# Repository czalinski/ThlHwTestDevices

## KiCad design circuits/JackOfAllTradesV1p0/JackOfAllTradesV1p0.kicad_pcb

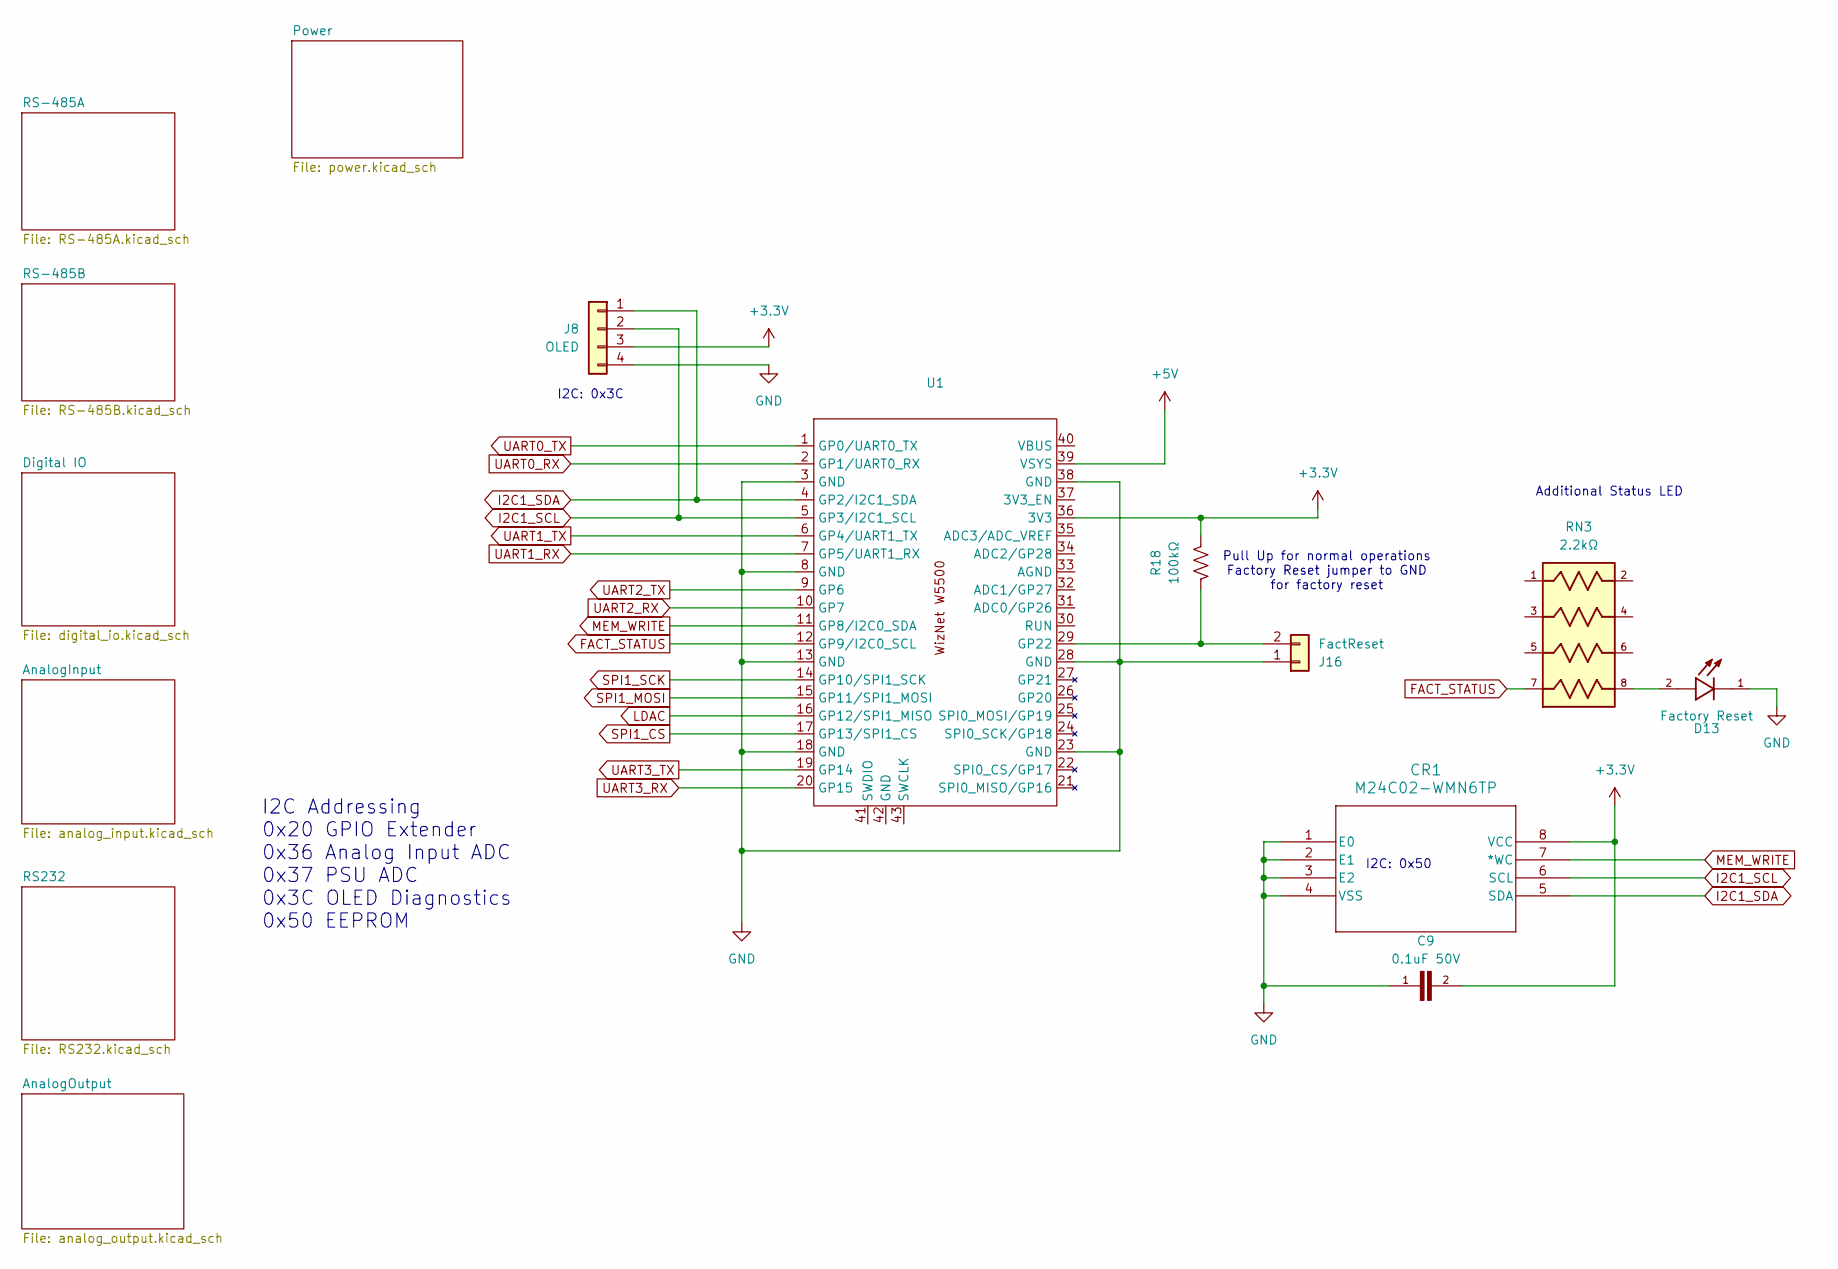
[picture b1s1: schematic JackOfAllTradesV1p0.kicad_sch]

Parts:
C9: 0.1uF 50V; CAPC2012X70
CR1: M24C02-WMN6TP; SO-8_STM
D13: Factory Reset; LED_LTST-C170GKT; PARTREV I
J8: OLED; PinHeader_1x04_P2.54mm_Vertical
J16: FactReset; PinHeader_1x02_P2.54mm_Horizontal
R18: 100kΩ; RES_1206
RN3: 2.2kΩ; RESCAXS50P200X100X55-8N
U1: WizNetPico_OnBoard

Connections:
+3.3V: C9.2, CR1.8 (VCC), J8.3, R18.1, U1.36 (3V3); also elsewhere on the board
+5V: U1.39 (VSYS); also elsewhere on the board
FACT_STATUS: RN3.7, U1.12 (GP9/I2C0_SCL)
GND: C9.1, CR1.1 (E0), CR1.2 (E1), CR1.3 (E2), CR1.4 (VSS), D13.1, J8.4, J16.1, U1.3 (GND), U1.8 (GND), U1.13 (GND), U1.18 (GND), U1.23 (GND), U1.28 (GND), U1.38 (GND); also elsewhere on the board
I2C1_SCL: CR1.6 (SCL), J8.2, U1.5 (GP3/I2C1_SCL); also elsewhere on the board
I2C1_SDA: CR1.5 (SDA), J8.1, U1.4 (GP2/I2C1_SDA); also elsewhere on the board
LDAC: U1.16 (GP12/SPI1_MISO); also elsewhere on the board
MEM_WRITE: CR1.7 (*WC), U1.11 (GP8/I2C0_SDA)
unnamed: D13.2, RN3.8
unnamed: J16.2, R18.2, U1.29 (GP22)
SPI1_CS: U1.17 (GP13/SPI1_CS); also elsewhere on the board
SPI1_MOSI: U1.15 (GP11/SPI1_MOSI); also elsewhere on the board
SPI1_SCK: U1.14 (GP10/SPI1_SCK); also elsewhere on the board
UART0_RX: U1.2 (GP1/UART0_RX); also elsewhere on the board
UART0_TX: U1.1 (GP0/UART0_TX); also elsewhere on the board
UART1_RX: U1.7 (GP5/UART1_RX); also elsewhere on the board
UART1_TX: U1.6 (GP4/UART1_TX); also elsewhere on the board
UART2_RX: U1.10 (GP7); also elsewhere on the board
UART2_TX: U1.9 (GP6); also elsewhere on the board
UART3_RX: U1.20 (GP15); also elsewhere on the board
UART3_TX: U1.19 (GP14); also elsewhere on the board

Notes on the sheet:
Pull Up for normal operations Factory Reset jumper to GND for factory reset
I2C: 0x3C
Additional Status LED
I2C Addressing 0x20 GPIO Extender 0x36 Analog Input ADC 0x37 PSU ADC 0x3C OLED Diagnostics 0x50 EEPROM
I2C: 0x50

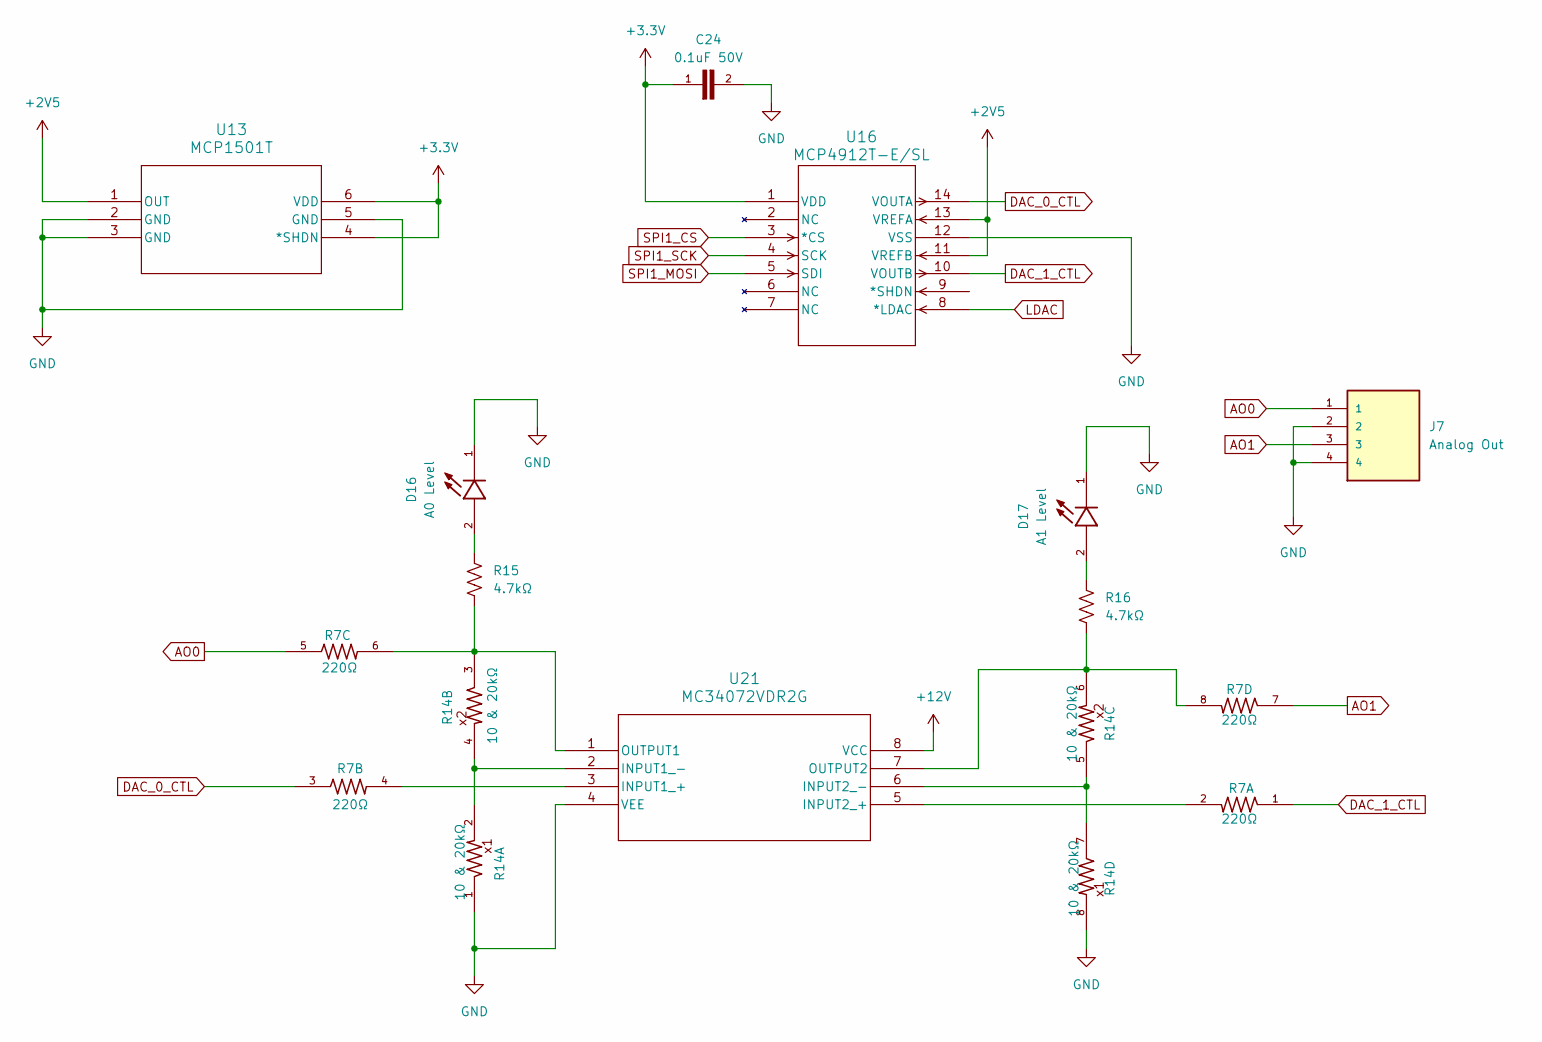
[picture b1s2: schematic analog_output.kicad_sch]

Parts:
C24: 0.1uF 50V; CAPC2012X70
D16: A0 Level; LED_LTST-C170GKT; PARTREV I
D17: A1 Level; LED_LTST-C170GKT; PARTREV I
J7: Analog Out; TE_1985218; PARTREV 29.03.2021
R7: 220Ω; RESCAV80P320X160X70-8N
R14: 10 & 20kΩ; RESCAV80P320X160X70-8N
R15, R16: 4.7kΩ; RES_1206
U13: MCP1501T; SOT-23_OT&slash_OTY_MCH
U16: MCP4912T-E/SL; SOIC14-N_MC_MCH
U21: MC34072VDR2G; SOIC8_ONS

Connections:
+2V5: U13.1 (OUT), U16.11 (VREFB), U16.13 (VREFA)
+3.3V: C24.1, U13.4 (*SHDN), U13.6 (VDD), U16.1 (VDD); also elsewhere on the board
+12V: U21.8 (VCC); also elsewhere on the board
AO0: J7.1, R7.5
AO1: J7.3, R7.7
DAC_0_CTL: R7.3, U16.14 (VOUTA)
DAC_1_CTL: R7.1, U16.10 (VOUTB)
GND: C24.2, D16.1, D17.1, J7.2, J7.4, R14.1, R14.8, U13.2 (GND), U13.3 (GND), U13.5 (GND), U16.12 (VSS), U21.4 (VEE); also elsewhere on the board
LDAC: U16.8 (*LDAC); also elsewhere on the board
unnamed: D16.2, R15.1
unnamed: D17.2, R16.1
unnamed: R7.4, U21.3 (INPUT1_+)
unnamed: R14.2, R14.4, U21.2 (INPUT1_-)
unnamed: R7.2, U21.5 (INPUT2_+)
unnamed: R14.5, R14.7, U21.6 (INPUT2_-)
unnamed: R7.6, R14.3, R15.2, U21.1 (OUTPUT1)
unnamed: R7.8, R14.6, R16.2, U21.7 (OUTPUT2)
SPI1_CS: U16.3 (*CS); also elsewhere on the board
SPI1_MOSI: U16.5 (SDI); also elsewhere on the board
SPI1_SCK: U16.4 (SCK); also elsewhere on the board

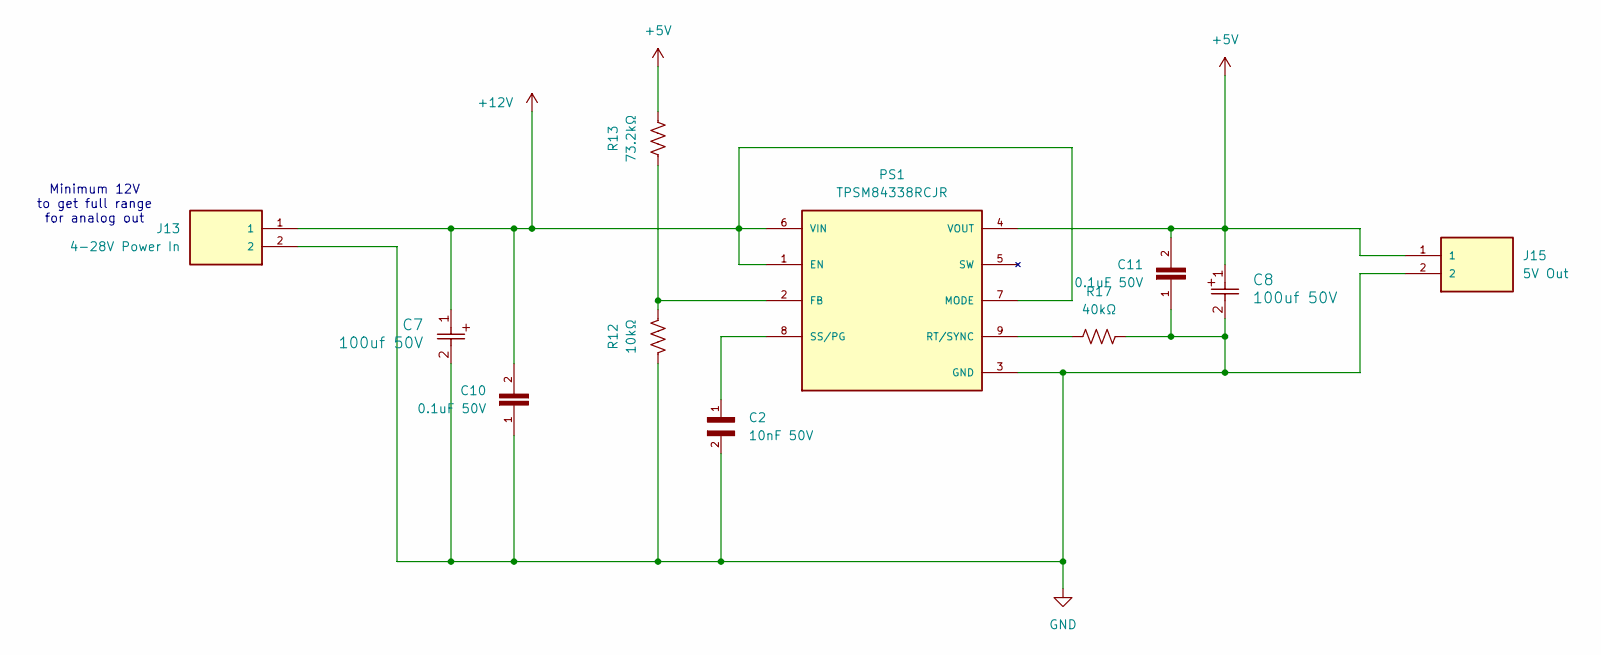
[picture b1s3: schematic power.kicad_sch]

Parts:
C2: 10nF 50V; CAPC3216X90N; PARTREV Jul. 2024
C7, C8: 100uf 50V; CAP_YX_8X11P5_RUB
C10, C11: 0.1uF 50V; CAPC2012X70
J13: 4-28V Power In; CUI_TB005-762-02BE
J15: 5V Out; CUI_TB005-762-02BE
PS1: TPSM84338RCJR; CONV_TPSM84338RCJR; PARTREV November 2024
R12: 10kΩ; RES_1206
R13: 73.2kΩ; RES_1206
R17: 40kΩ; RES_1206

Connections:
+5V: C8.1, C11.2, J15.1, PS1.4 (VOUT_4), PS1.4_1 (VOUT_4), PS1.4_2 (VOUT_4), PS1.4_3 (VOUT_4), PS1.4_4 (VOUT_4), PS1.4_5 (VOUT_4), PS1.4_6 (VOUT_4), R13.2; also elsewhere on the board
+12V: C7.1, C10.2, J13.1, PS1.1 (EN_1), PS1.6 (VIN_6), PS1.7 (MODE_7); also elsewhere on the board
GND: C2.2, C7.2, C8.2, C10.1, C11.1, J13.2, J15.2, PS1.3 (GND_3), R12.2, R17.2; also elsewhere on the board
unnamed: PS1.2 (FB_2), R12.1, R13.1
unnamed: PS1.9 (RT/SYNC_9), R17.1
unnamed: C2.1, PS1.8 (SS/PG_8)

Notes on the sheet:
Minimum 12V to get full range for analog out

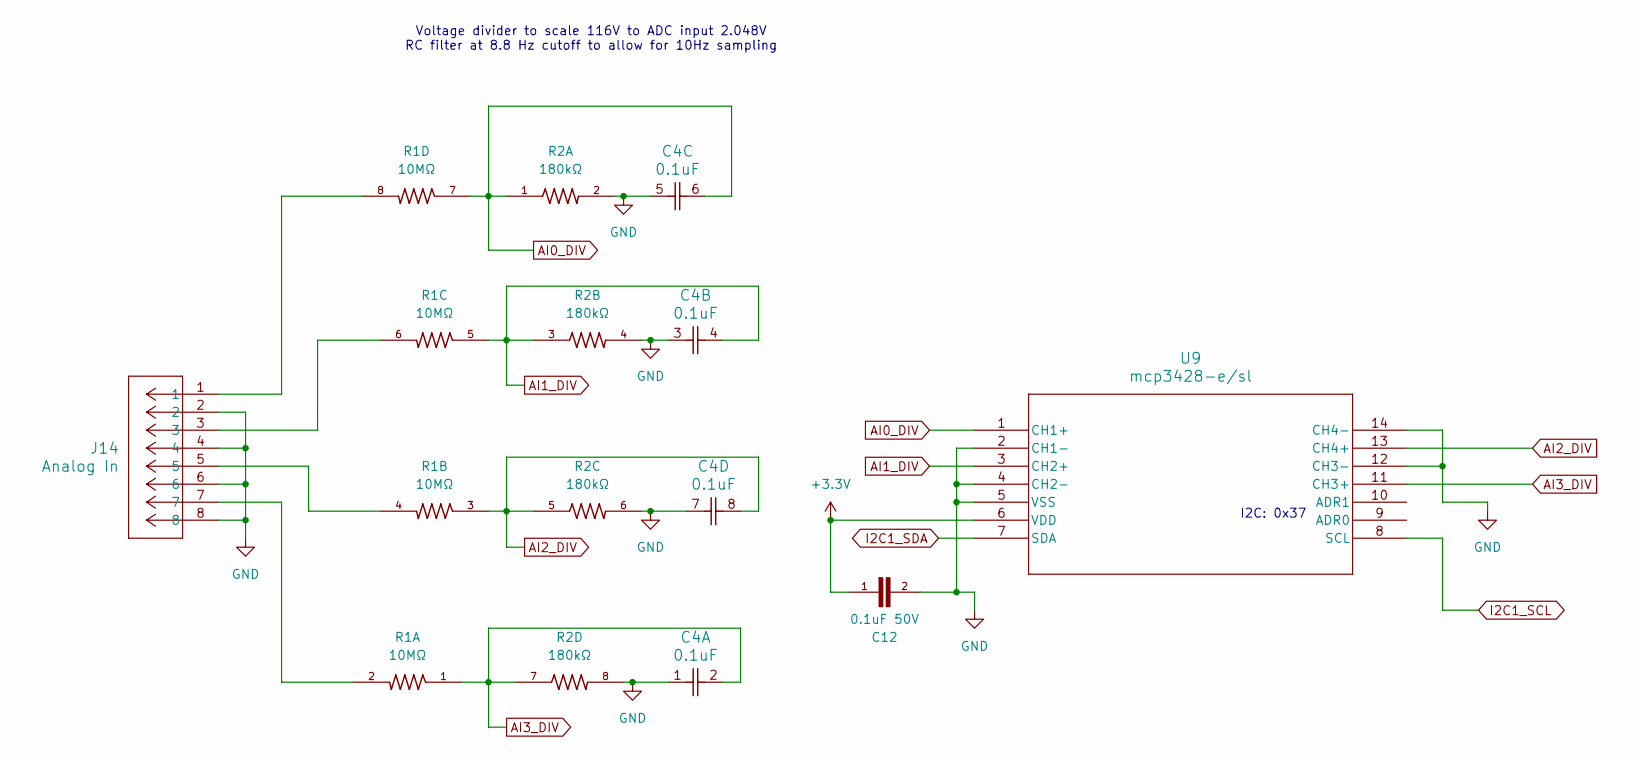
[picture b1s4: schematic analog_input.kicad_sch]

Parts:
C4: 0.1uF; CAP_CA0612_3P2X1P6_YAG
C12: 0.1uF 50V; CAPC2012X70
J14: Analog In; CONN_1989803_PXC
R1: 10MΩ; RESCAV80P320X160X70-8N
R2: 180kΩ; RESCAV80P320X160X70-8N
U9: mcp3428-e/sl; SOIC14-N_MC_MCH

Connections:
+3.3V: C12.1, U9.6 (VDD); also elsewhere on the board
AI0_DIV: C4.6, R1.7, R2.1, U9.1 (CH1+)
AI1_DIV: C4.4, R1.5, R2.3, U9.3 (CH2+)
AI2_DIV: C4.8, R1.3, R2.5, U9.13 (CH4+)
AI3_DIV: C4.2, R1.1, R2.7, U9.11 (CH3+)
GND: C4.1, C4.3, C4.5, C4.7, C12.2, J14.2, J14.4, J14.6, J14.8, R2.2, R2.4, R2.6, R2.8, U9.2 (CH1-), U9.4 (CH2-), U9.5 (VSS), U9.12 (CH3-), U9.14 (CH4-); also elsewhere on the board
I2C1_SCL: U9.8 (SCL); also elsewhere on the board
I2C1_SDA: U9.7 (SDA); also elsewhere on the board
unnamed: J14.1, R1.8
unnamed: J14.3, R1.6
unnamed: J14.5, R1.4
unnamed: J14.7, R1.2

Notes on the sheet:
Voltage divider to scale 116V to ADC input 2.048V RC filter at 8.8 Hz cutoff to allow for 10Hz sampling
I2C: 0x37

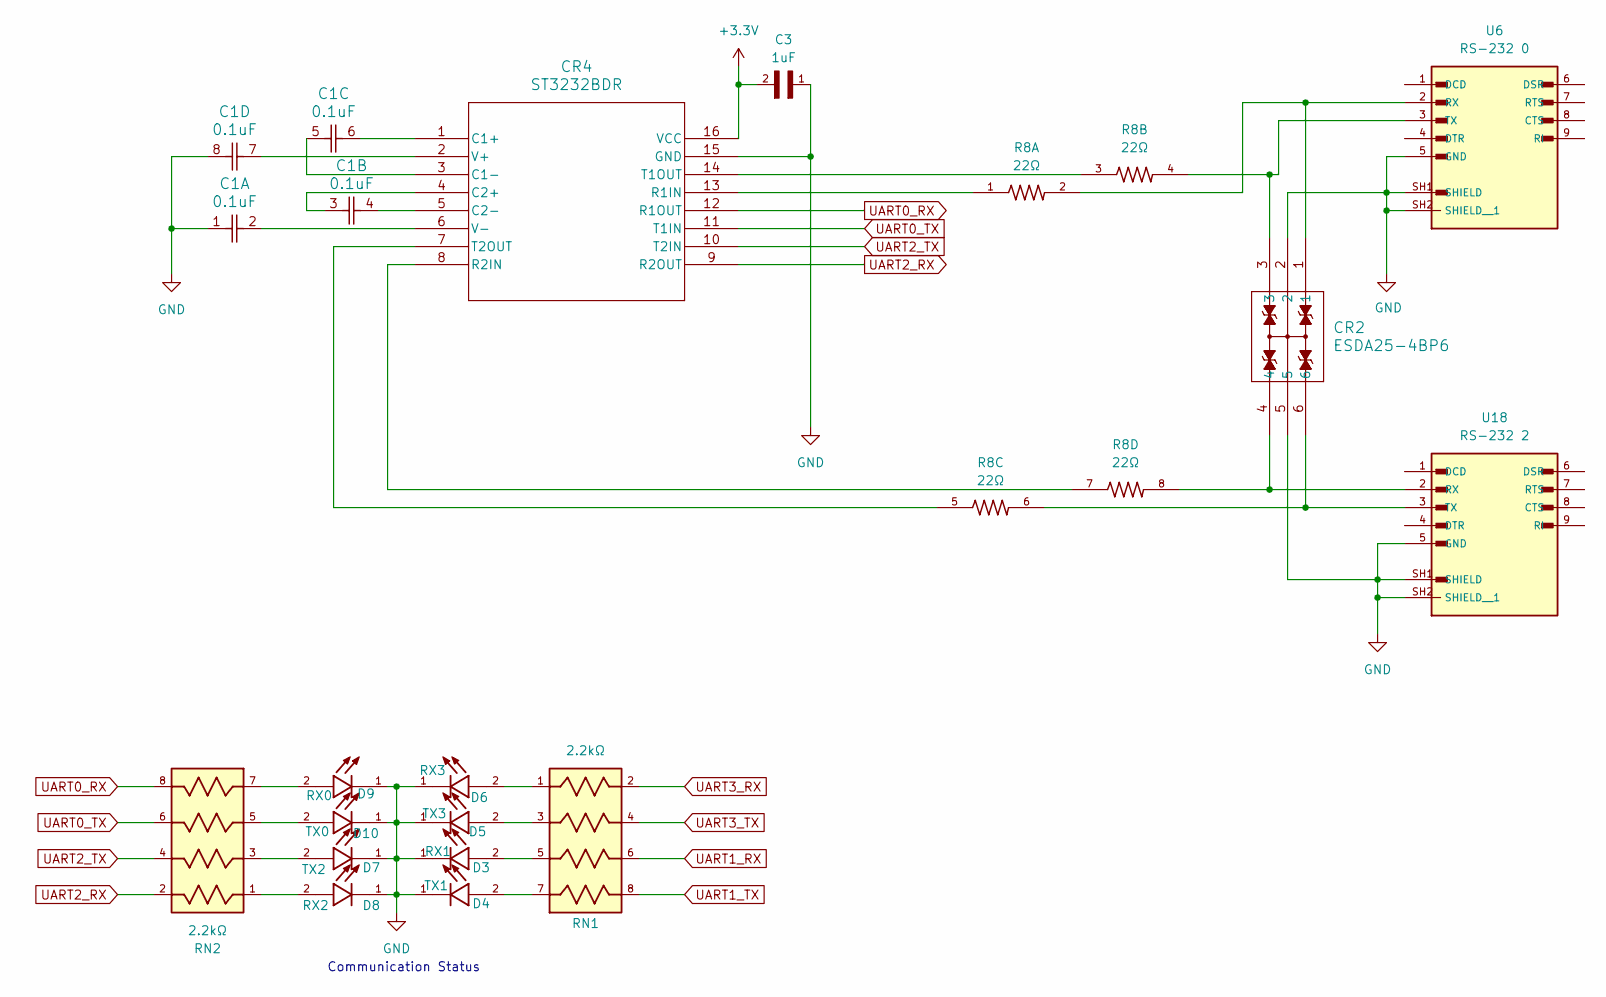
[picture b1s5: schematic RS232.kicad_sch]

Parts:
C1: 0.1uF; CAP_CA0612_3P2X1P6_YAG
C3: 1uF; CAPC1608X90N
CR2: ESDA25-4BP6; SOT666_ESDA25_STM
CR4: ST3232BDR; SO-16_STM
D3: RX1; LED_LTST-C170GKT; PARTREV I
D4: TX1; LED_LTST-C170GKT; PARTREV I
D5: TX3; LED_LTST-C170GKT; PARTREV I
D6: RX3; LED_LTST-C170GKT; PARTREV I
D7: TX2; LED_LTST-C170GKT; PARTREV I
D8: RX2; LED_LTST-C170GKT; PARTREV I
D9: RX0; LED_LTST-C170GKT; PARTREV I
D10: TX0; LED_LTST-C170GKT; PARTREV I
R8: 22Ω; RESCAV80P320X160X70-8N
RN1, RN2: 2.2kΩ; RESCAXS50P200X100X55-8N
U6: RS-232 0; ASSMANN_A-DS_09_A_KG-T2S
U18: RS-232 2; ASSMANN_A-DS_09_A_KG-T2S

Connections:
+3.3V: C3.2, CR4.16 (VCC); also elsewhere on the board
GND: C1.1, C1.8, C3.1, CR2.2, CR2.5, CR4.15 (GND), D3.1, D4.1, D5.1, D6.1, D7.1, D8.1, D9.1, D10.1, U6.5 (GND), U6.SH1 (SHIELD), U6.SH2 (SHIELD__1), U18.5 (GND), U18.SH1 (SHIELD), U18.SH2 (SHIELD__1); also elsewhere on the board
unnamed: C1.6, CR4.1 (C1+)
unnamed: C1.5, CR4.3 (C1-)
unnamed: C1.3, CR4.4 (C2+)
unnamed: C1.4, CR4.5 (C2-)
unnamed: CR4.13 (R1IN), R8.1
unnamed: CR4.8 (R2IN), R8.7
unnamed: CR4.14 (T1OUT), R8.3
unnamed: CR4.7 (T2OUT), R8.5
unnamed: C1.7, CR4.2 (V+)
unnamed: C1.2, CR4.6 (V-)
unnamed: D3.2, RN1.5
unnamed: D4.2, RN1.7
unnamed: D5.2, RN1.3
unnamed: D6.2, RN1.1
unnamed: D7.2, RN2.3
unnamed: D8.2, RN2.1
unnamed: D9.2, RN2.7
unnamed: D10.2, RN2.5
unnamed: CR2.1, R8.2, U6.2 (RX)
unnamed: CR2.3, R8.4, U6.3 (TX)
unnamed: CR2.4, R8.8, U18.2 (RX)
unnamed: CR2.6, R8.6, U18.3 (TX)
UART0_RX: CR4.12 (R1OUT), RN2.8; also elsewhere on the board
UART0_TX: CR4.11 (T1IN), RN2.6; also elsewhere on the board
UART1_RX: RN1.6; also elsewhere on the board
UART1_TX: RN1.8; also elsewhere on the board
UART2_RX: CR4.9 (R2OUT), RN2.2; also elsewhere on the board
UART2_TX: CR4.10 (T2IN), RN2.4; also elsewhere on the board
UART3_RX: RN1.2; also elsewhere on the board
UART3_TX: RN1.4; also elsewhere on the board

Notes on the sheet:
Communication Status

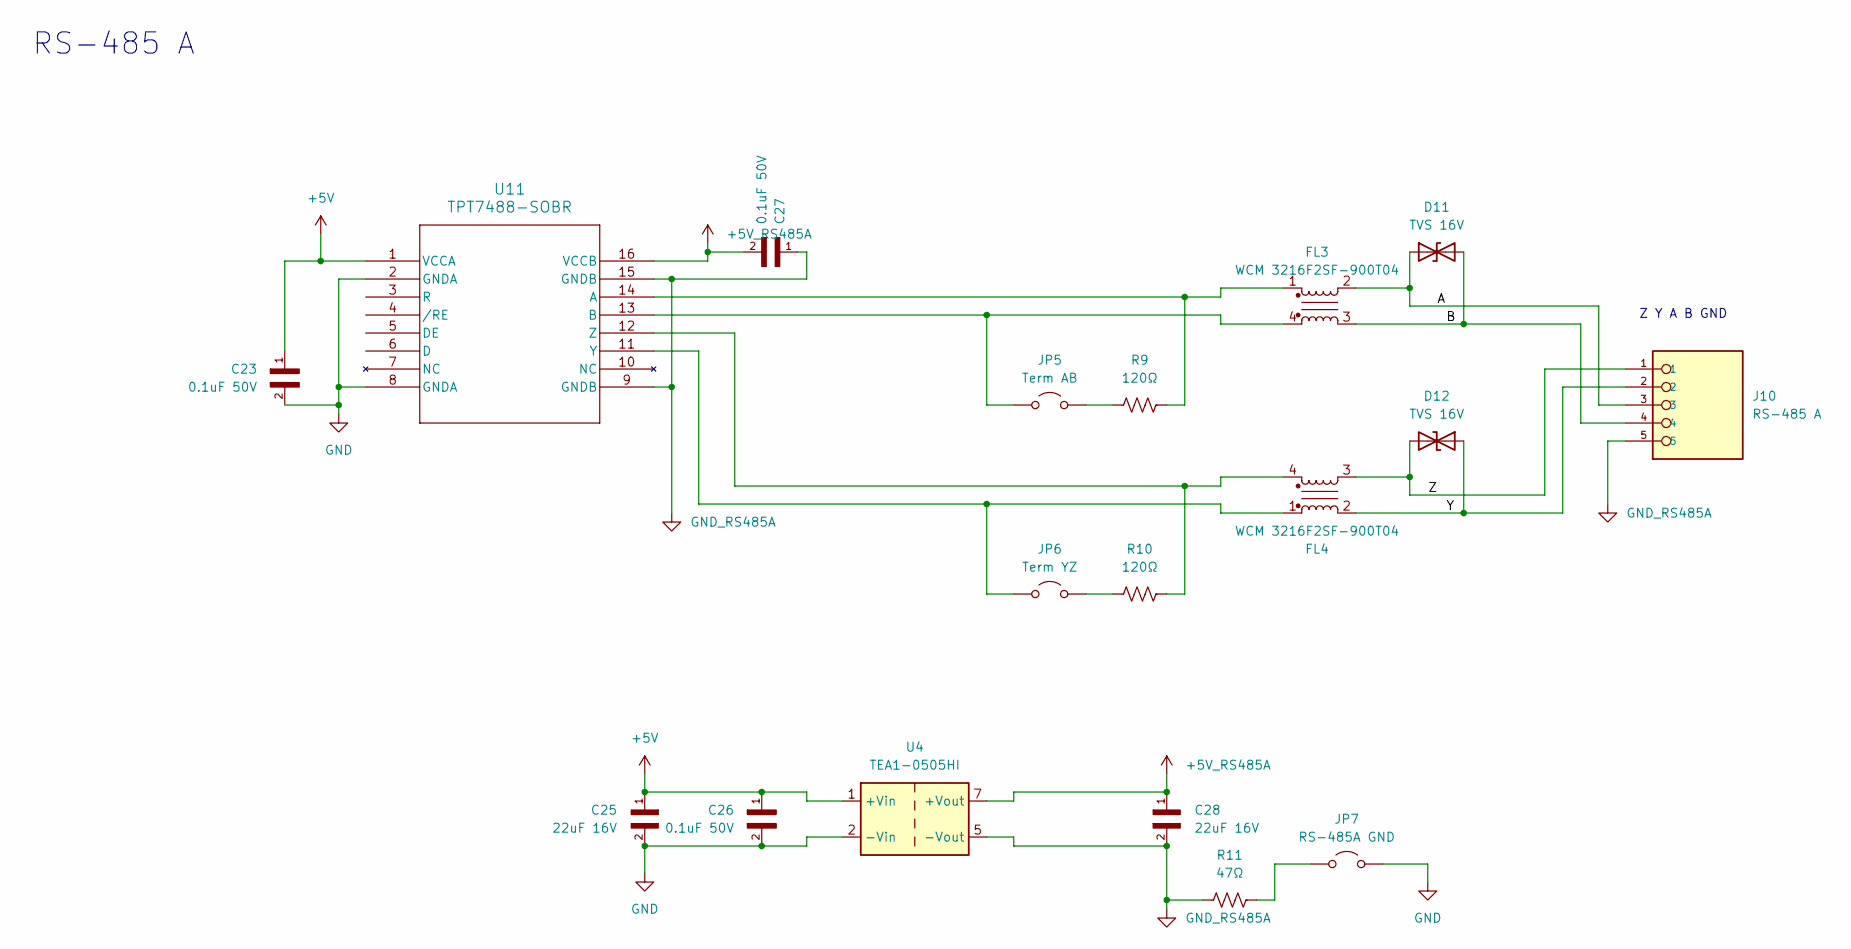
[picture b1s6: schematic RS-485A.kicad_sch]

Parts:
C23, C26, C27: 0.1uF 50V; CAPC2012X70
C25, C28: 22uF 16V; CAPC3216X95N
D11, D12: TVS 16V; D_SOD-123F
FL3, FL4: WCM 3216F2SF-900T04; WCM 3216F2SF-900T04-1206
J10: RS-485 A; PHOENIX_1990038
JP5: Term AB; PinHeader_1x02_P2.54mm_Vertical
JP6: Term YZ; PinHeader_1x02_P2.54mm_Vertical
JP7: RS-485A GND; PinHeader_1x02_P2.54mm_Vertical
R9, R10: 120Ω; RES_1206
R11: 47Ω; RES_1206
U4: TEA1-0505HI; Converter_DCDC_TRACO_TEA1-xxxxHI_THT
U11: TPT7488-SOBR; SOBWSOP-16-A_TPK

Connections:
+5V: C23.1, C25.1, C26.1, U4.1 (+Vin), U11.1 (VCCA); also elsewhere on the board
+5V_RS485A: C27.2, C28.1, U4.7 (+Vout), U11.16 (VCCB)
/RS-485A/A: D11.1 (A1), FL3.2, J10.3
/RS-485A/B: D11.2 (A2), FL3.3, J10.4
/RS-485A/Y: D12.1 (A1), FL4.2, J10.2
/RS-485A/Z: D12.2 (A2), FL4.3, J10.1
GND: C23.2, C25.2, C26.2, JP7.1 (A), U4.2 (-Vin), U11.2 (GNDA), U11.8 (GNDA); also elsewhere on the board
GND_RS485A: C27.1, C28.2, J10.5, R11.1, U4.5 (-Vout), U11.9 (GNDB), U11.15 (GNDB)
unnamed: JP5.1 (A), R9.1
unnamed: FL3.4, JP5.2 (B), U11.13 (B)
unnamed: JP6.1 (A), R10.1
unnamed: FL4.1, JP6.2 (B), U11.11 (Y)
unnamed: JP7.2 (B), R11.2
unnamed: FL3.1, R9.2, U11.14 (A)
unnamed: FL4.4, R10.2, U11.12 (Z)

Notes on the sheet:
RS-485 A
Z Y A B GND

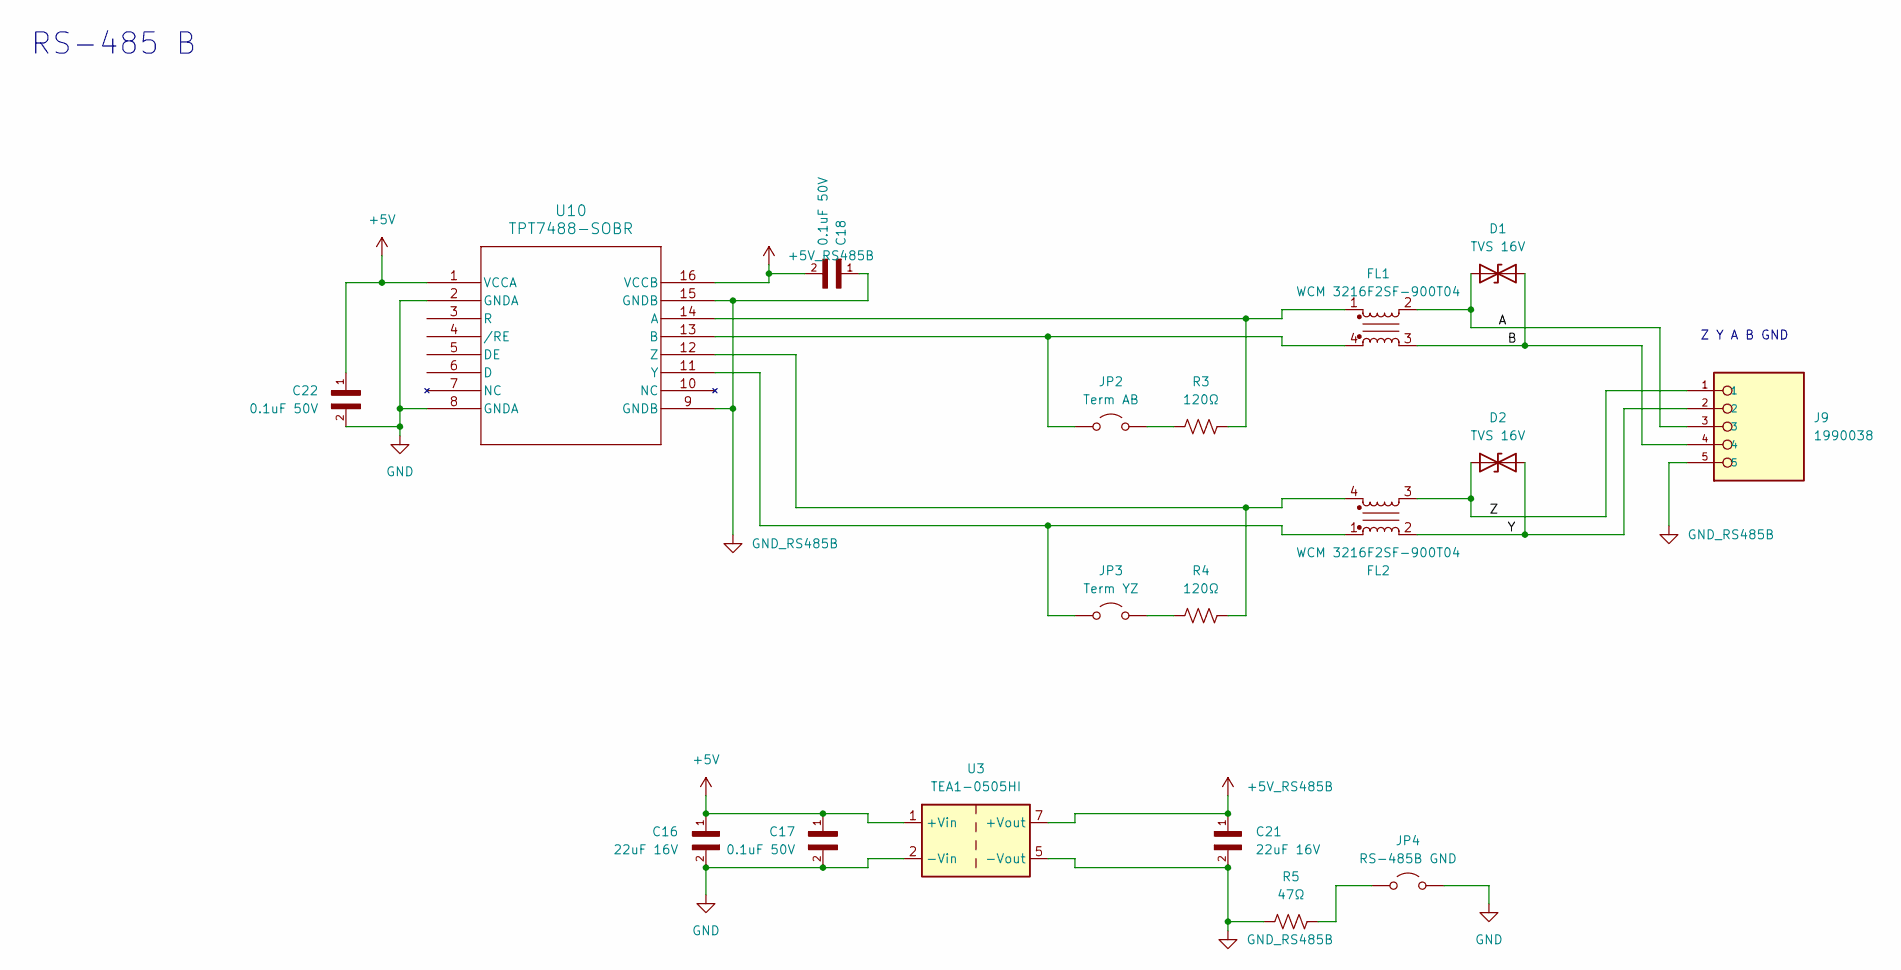
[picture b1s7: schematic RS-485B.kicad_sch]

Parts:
C16, C21: 22uF 16V; CAPC3216X95N
C17, C18, C22: 0.1uF 50V; CAPC2012X70
D1, D2: TVS 16V; D_SOD-123F
FL1, FL2: WCM 3216F2SF-900T04; WCM 3216F2SF-900T04-1206
J9: 1990038; PHOENIX_1990038
JP2: Term AB; PinHeader_1x02_P2.54mm_Vertical
JP3: Term YZ; PinHeader_1x02_P2.54mm_Vertical
JP4: RS-485B GND; PinHeader_1x02_P2.54mm_Vertical
R3, R4: 120Ω; RES_1206
R5: 47Ω; RES_1206
U3: TEA1-0505HI; Converter_DCDC_TRACO_TEA1-xxxxHI_THT
U10: TPT7488-SOBR; SOBWSOP-16-A_TPK

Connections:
+5V: C16.1, C17.1, C22.1, U3.1 (+Vin), U10.1 (VCCA); also elsewhere on the board
+5V_RS485B: C18.2, C21.1, U3.7 (+Vout), U10.16 (VCCB)
/RS-485B/A: D1.1 (A1), FL1.2, J9.3
/RS-485B/B: D1.2 (A2), FL1.3, J9.4
/RS-485B/Y: D2.2 (A2), FL2.2, J9.2
/RS-485B/Z: D2.1 (A1), FL2.3, J9.1
GND: C16.2, C17.2, C22.2, JP4.1 (A), U3.2 (-Vin), U10.2 (GNDA), U10.8 (GNDA); also elsewhere on the board
GND_RS485B: C18.1, C21.2, J9.5, R5.1, U3.5 (-Vout), U10.9 (GNDB), U10.15 (GNDB)
unnamed: JP2.1 (A), R3.1
unnamed: FL1.4, JP2.2 (B), U10.13 (B)
unnamed: JP3.1 (A), R4.1
unnamed: FL2.1, JP3.2 (B), U10.11 (Y)
unnamed: JP4.2 (B), R5.2
unnamed: FL1.1, R3.2, U10.14 (A)
unnamed: FL2.4, R4.2, U10.12 (Z)

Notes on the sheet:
RS-485 B
Z Y A B GND

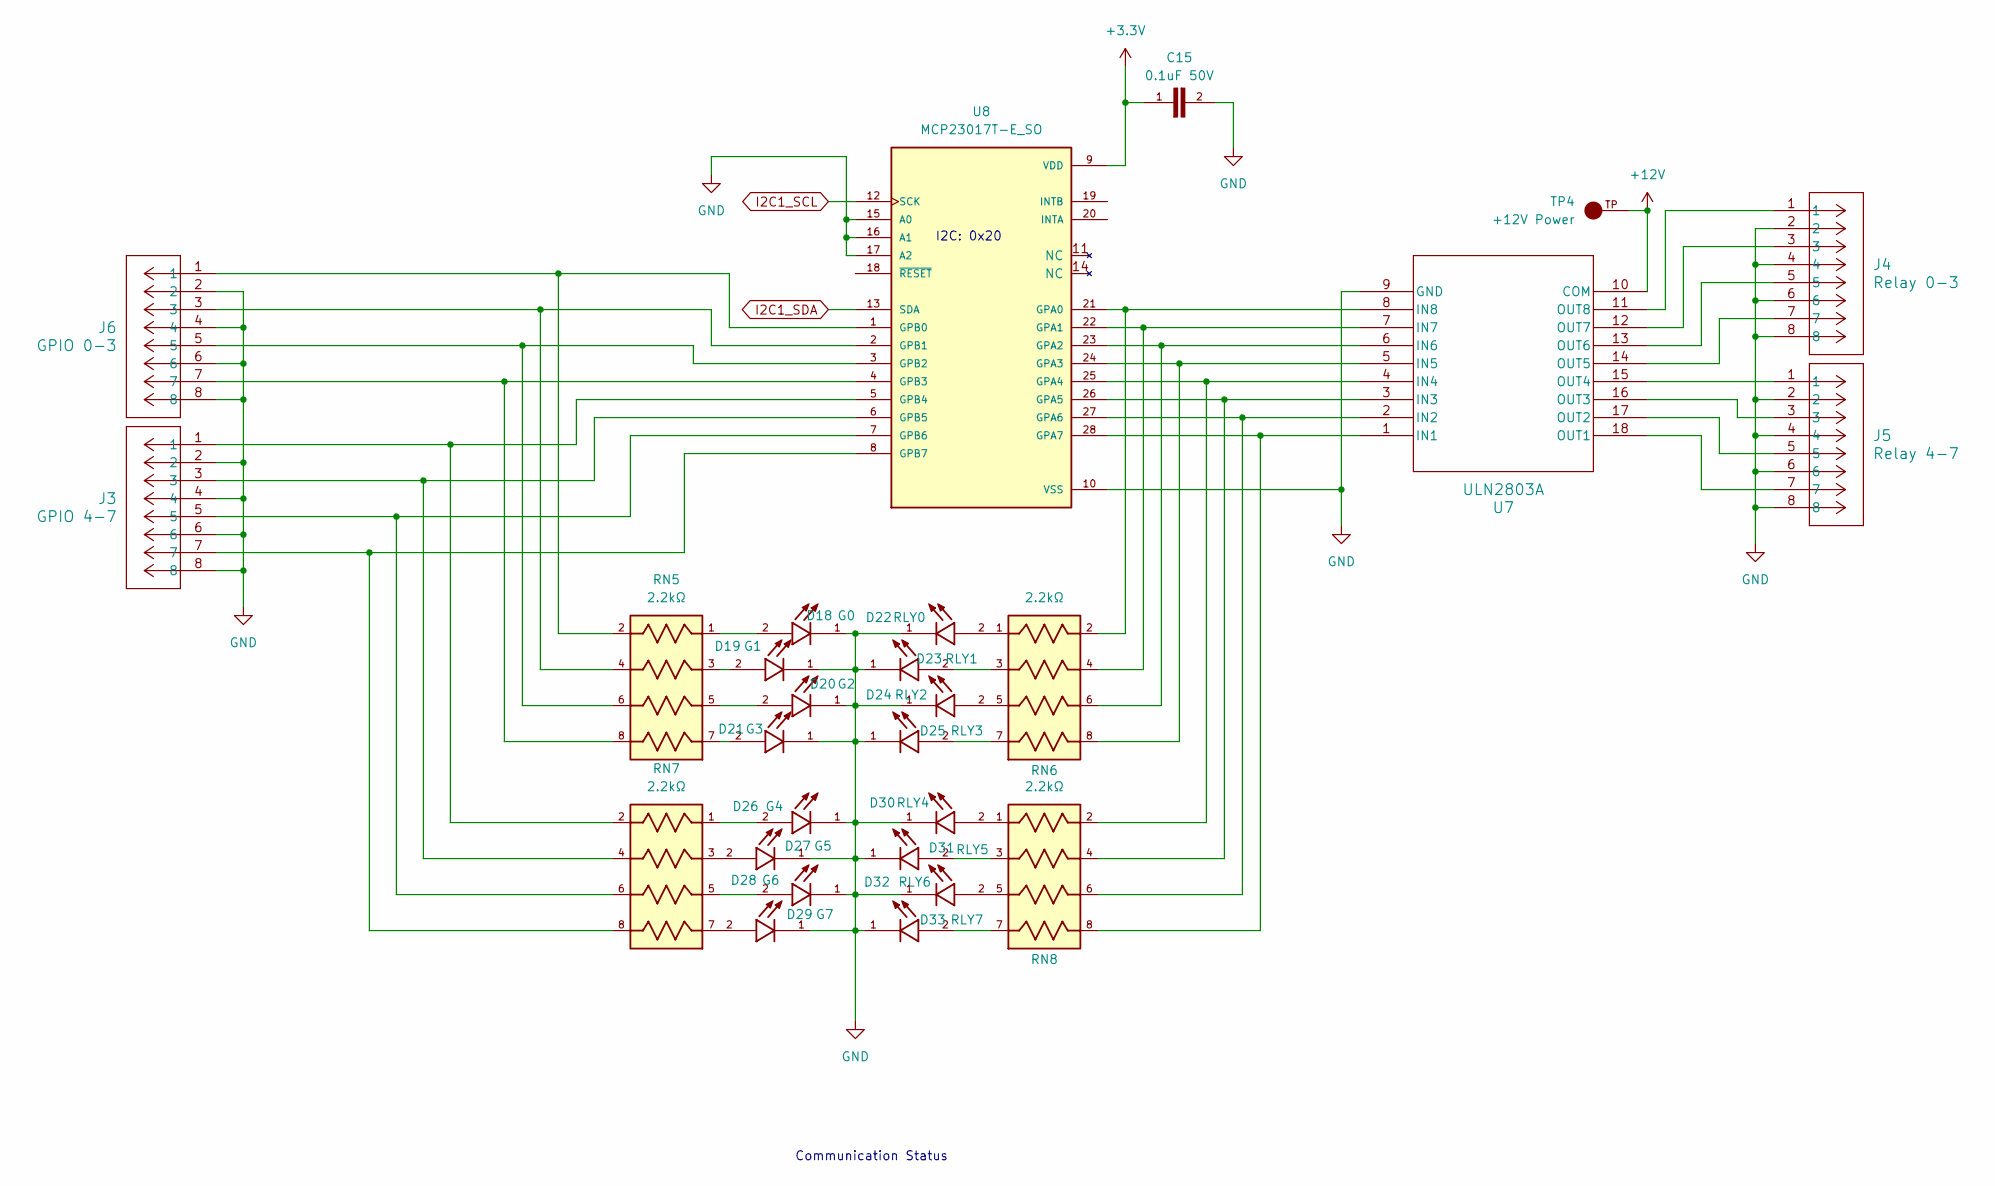
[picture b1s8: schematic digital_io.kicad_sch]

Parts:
C15: 0.1uF 50V; CAPC2012X70
D18: G0; LED_LTST-C170GKT; PARTREV I
D19: G1; LED_LTST-C170GKT; PARTREV I
D20: G2; LED_LTST-C170GKT; PARTREV I
D21: G3; LED_LTST-C170GKT; PARTREV I
D22: RLY0; LED_LTST-C170GKT; PARTREV I
D23: RLY1; LED_LTST-C170GKT; PARTREV I
D24: RLY2; LED_LTST-C170GKT; PARTREV I
D25: RLY3; LED_LTST-C170GKT; PARTREV I
D26: G4; LED_LTST-C170GKT; PARTREV I
D27: G5; LED_LTST-C170GKT; PARTREV I
D28: G6; LED_LTST-C170GKT; PARTREV I
D29: G7; LED_LTST-C170GKT; PARTREV I
D30: RLY4; LED_LTST-C170GKT; PARTREV I
D31: RLY5; LED_LTST-C170GKT; PARTREV I
D32: RLY6; LED_LTST-C170GKT; PARTREV I
D33: RLY7; LED_LTST-C170GKT; PARTREV I
J3: GPIO 4-7; CONN_1989803_PXC
J4: Relay 0-3; CONN_1989803_PXC
J5: Relay 4-7; CONN_1989803_PXC
J6: GPIO 0-3; CONN_1989803_PXC
RN5, RN6, RN7, RN8: 2.2kΩ; RESCAXS50P200X100X55-8N
TP4: +12V Power; KEYSTONE_4954_Slot; PARTREV B; DigiKey_Part_Number 36-4954-ND
U7: ULN2803A; SOIC-18W_7.5x11.6mm_P1.27mm
U8: MCP23017T-E_SO; SOIC127P1030X265-28N

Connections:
+3.3V: C15.1, U8.9 (VDD); also elsewhere on the board
+12V: TP4.TP, U7.10 (COM); also elsewhere on the board
GND: C15.2, D18.1, D19.1, D20.1, D21.1, D22.1, D23.1, D24.1, D25.1, D26.1, D27.1, D28.1, D29.1, D30.1, D31.1, D32.1, D33.1, J3.2, J3.4, J3.6, J3.8, J4.2, J4.4, J4.6, J4.8, J5.2, J5.4, J5.6, J5.8, J6.2, J6.4, J6.6, J6.8, U7.9 (GND), U8.10 (VSS), U8.15 (A0), U8.16 (A1), U8.17 (A2); also elsewhere on the board
I2C1_SCL: U8.12 (SCK); also elsewhere on the board
I2C1_SDA: U8.13 (SDA); also elsewhere on the board
unnamed: D18.2, RN5.1
unnamed: D19.2, RN5.3
unnamed: D20.2, RN5.5
unnamed: D21.2, RN5.7
unnamed: D22.2, RN6.1
unnamed: D23.2, RN6.3
unnamed: D24.2, RN6.5
unnamed: D25.2, RN6.7
unnamed: D26.2, RN7.1
unnamed: D27.2, RN7.3
unnamed: D28.2, RN7.5
unnamed: D29.2, RN7.7
unnamed: D30.2, RN8.1
unnamed: D31.2, RN8.3
unnamed: D32.2, RN8.5
unnamed: D33.2, RN8.7
unnamed: RN8.8, U7.1 (IN1), U8.28 (GPA7)
unnamed: RN8.6, U7.2 (IN2), U8.27 (GPA6)
unnamed: RN8.4, U7.3 (IN3), U8.26 (GPA5)
unnamed: RN8.2, U7.4 (IN4), U8.25 (GPA4)
unnamed: RN6.8, U7.5 (IN5), U8.24 (GPA3)
unnamed: RN6.6, U7.6 (IN6), U8.23 (GPA2)
unnamed: RN6.4, U7.7 (IN7), U8.22 (GPA1)
unnamed: RN6.2, U7.8 (IN8), U8.21 (GPA0)
unnamed: J5.7, U7.18 (OUT1)
unnamed: J5.5, U7.17 (OUT2)
unnamed: J5.3, U7.16 (OUT3)
unnamed: J5.1, U7.15 (OUT4)
unnamed: J4.7, U7.14 (OUT5)
unnamed: J4.5, U7.13 (OUT6)
unnamed: J4.3, U7.12 (OUT7)
unnamed: J4.1, U7.11 (OUT8)
unnamed: J6.1, RN5.2, U8.1 (GPB0)
unnamed: J6.3, RN5.4, U8.2 (GPB1)
unnamed: J6.5, RN5.6, U8.3 (GPB2)
unnamed: J6.7, RN5.8, U8.4 (GPB3)
unnamed: J3.1, RN7.2, U8.5 (GPB4)
unnamed: J3.3, RN7.4, U8.6 (GPB5)
unnamed: J3.5, RN7.6, U8.7 (GPB6)
unnamed: J3.7, RN7.8, U8.8 (GPB7)

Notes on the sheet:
I2C: 0x20
Communication Status

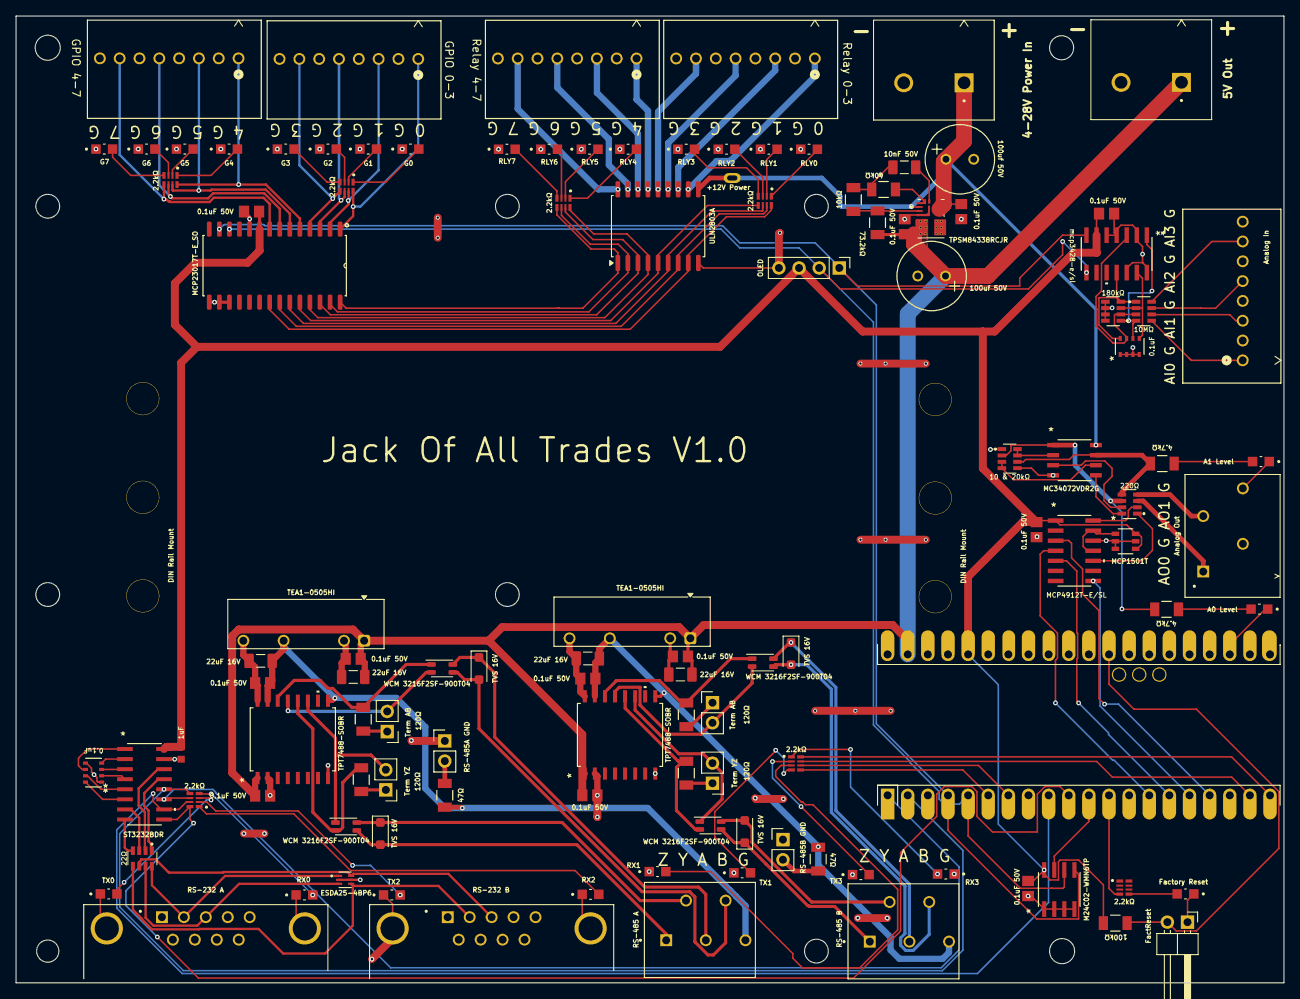
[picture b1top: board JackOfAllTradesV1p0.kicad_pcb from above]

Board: 2 copper layers, 160.0 x 122.0 mm, 117 parts (0 on the bottom side), 134 nets.
